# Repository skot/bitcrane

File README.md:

Bitcrane can fully control a Bitmain Antminer over a single USB connection.

- CERN Open Hardware License (OHL) v2
- [KiCad](https://kicad.org) design files
- Based on the Raspberry Pi RP2040
- Support for 3 Antminer hashboards
- Support for 4 fans with your choice of 1x4 or 2x2 connectors
- Controls Antminer S19/S21 style PSUs
- Bitcrane is powered by 5V from the USB-C connector
	- Attached fans are powered by standard Antminer 2x3 12V controlboard power

## TODO
- RP2040 firmware, based on [emberone-usbserial-fw](https://github.com/256foundation/emberone-usbserial-fw/tree/bitcrane-v3) bitcrane-v3 branch WIP
- [Mujina](https://mujina.org) mining firmware support.
- Custom Antminer faceplate.
- [Dismantle the proprietary Bitcoin mining empire](https://256foundation.org)

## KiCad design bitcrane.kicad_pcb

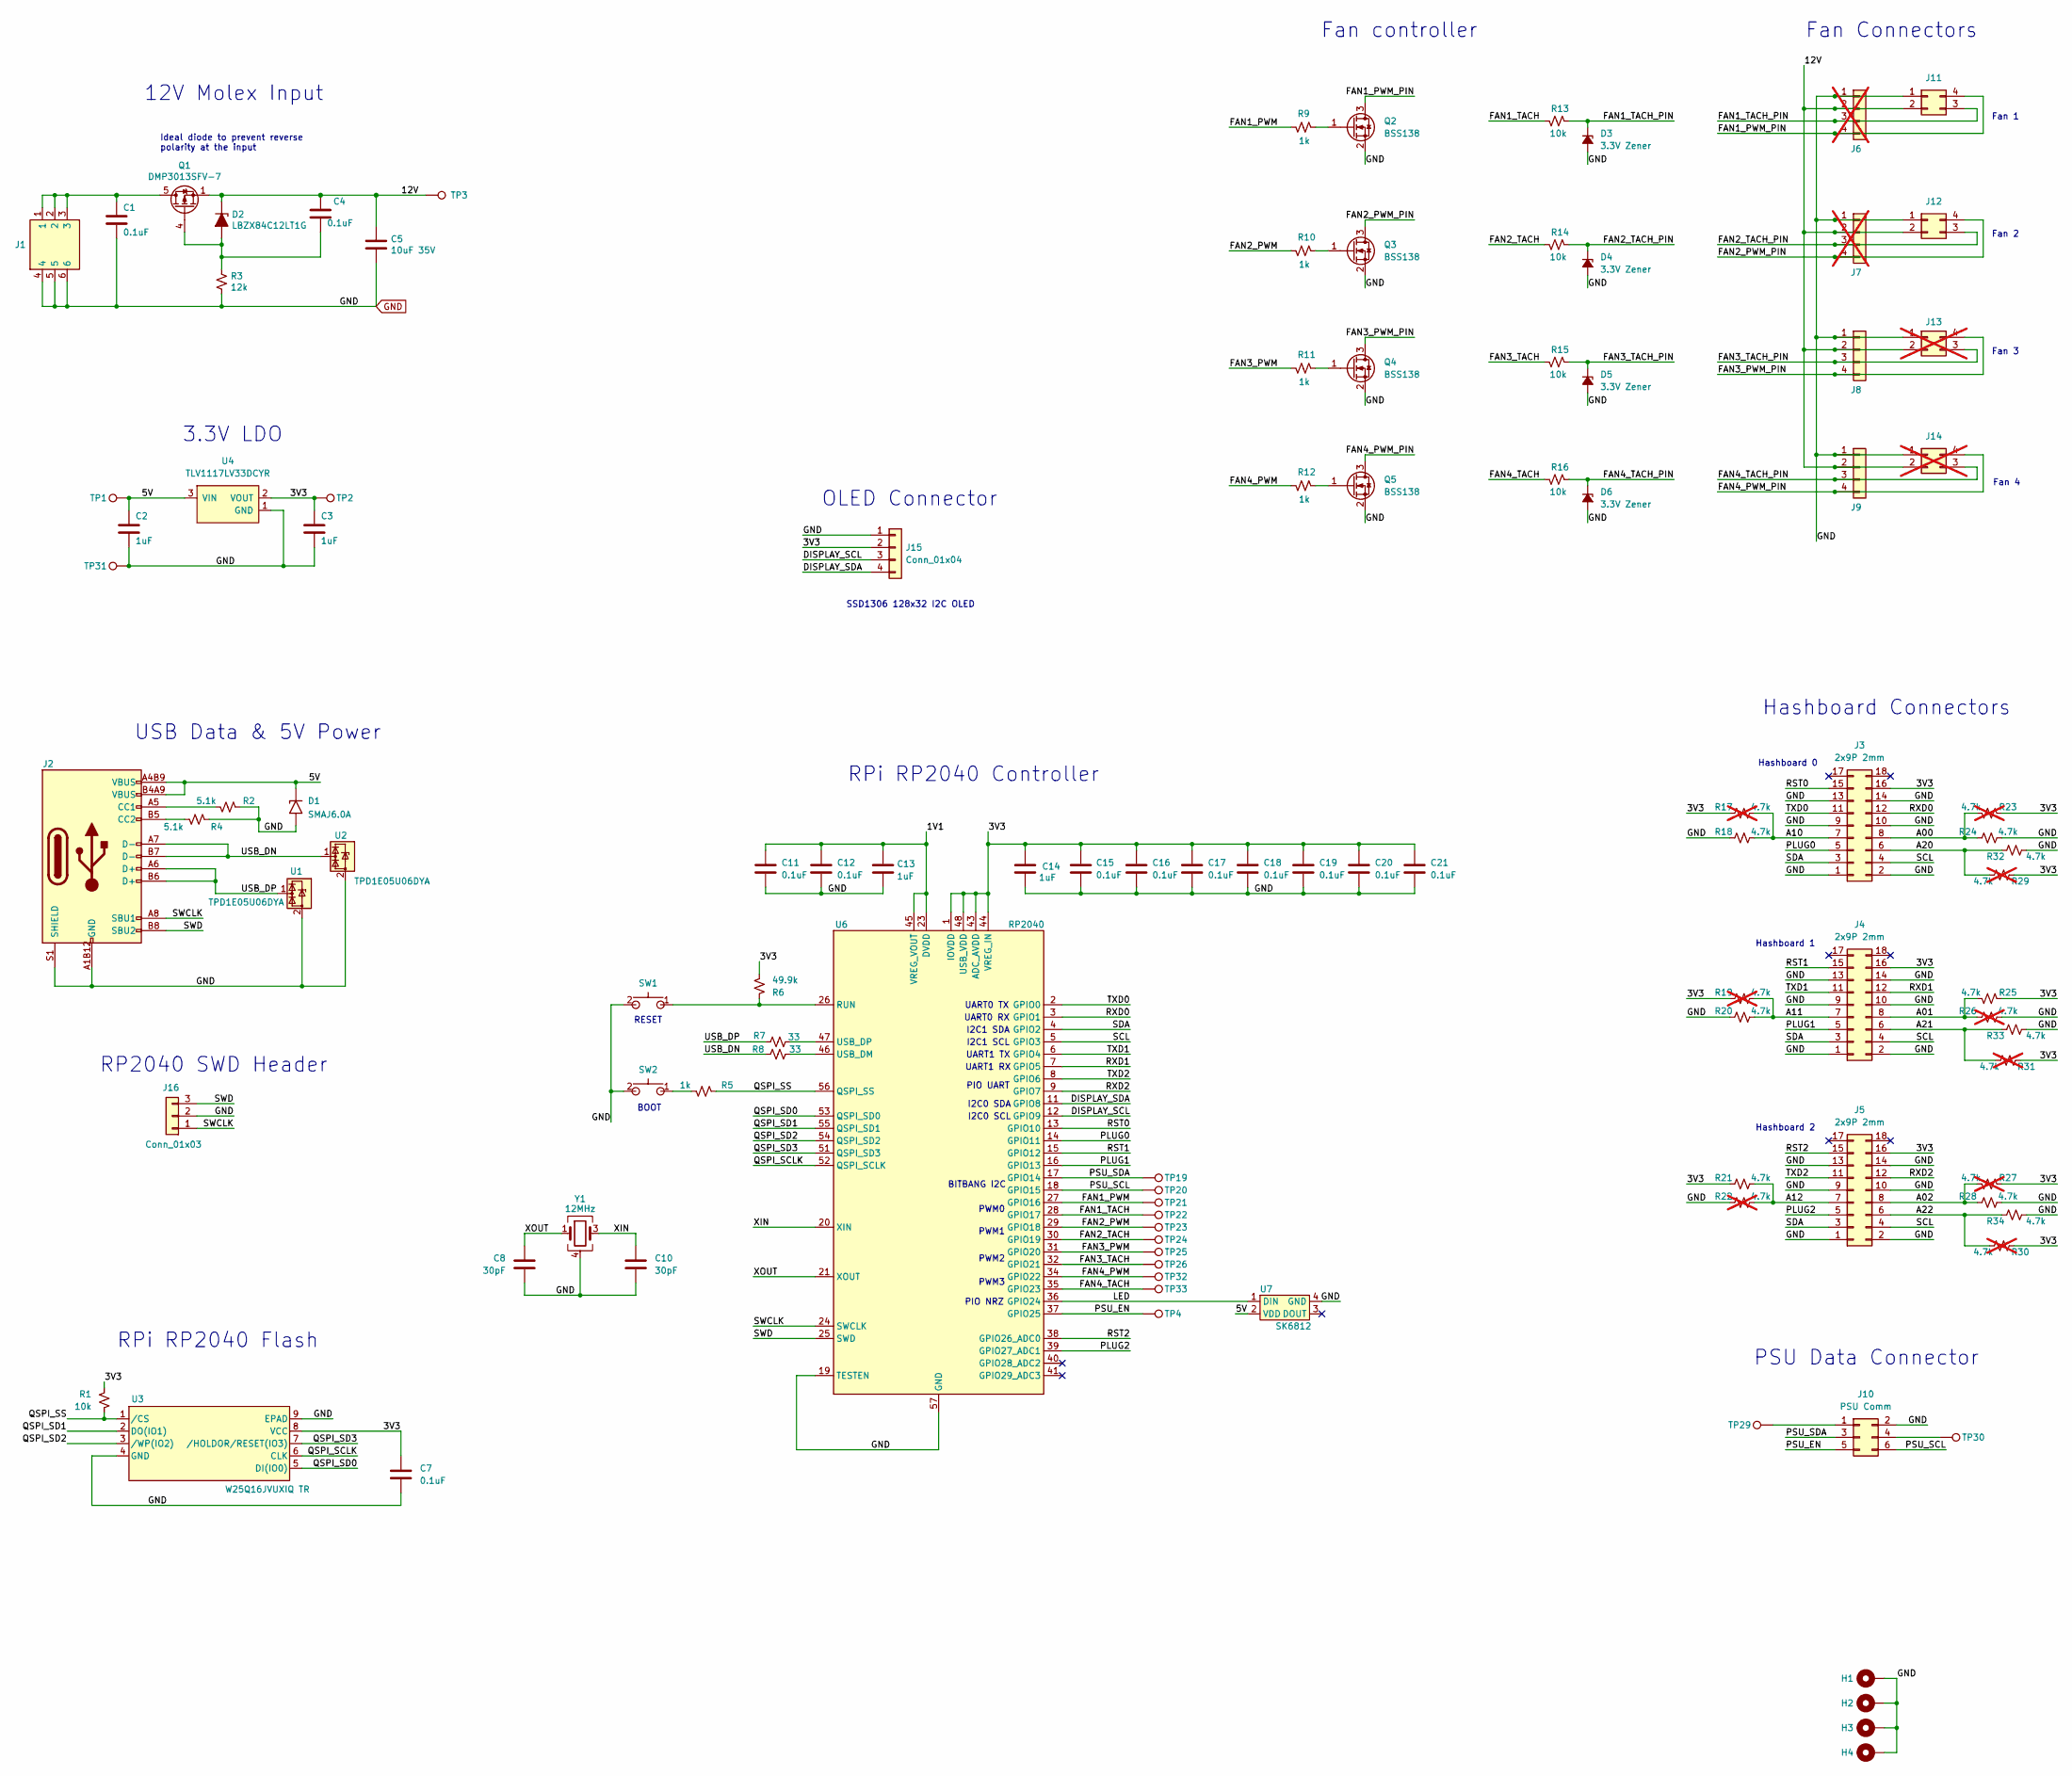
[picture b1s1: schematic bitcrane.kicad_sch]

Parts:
C1, C4, C7, C11, C12, C15, C16, C17, C18, C19, C20, C21: 0.1uF; C_0402_1005Metric; LCSC C307331
C2, C3, C13, C14: 1uF; C_0402_1005Metric; LCSC C52923
C5: 10uF 35V; C_0805_2012Metric; LCSC C440198
C8, C10: 30pF; C_0402_1005Metric; LCSC C1570
D1: SMAJ6.0A; D_SMB; LCSC C364284
D2: LBZX84C12LT1G; SOT-23-3_L2.9-W1.6-P1.90-LS2.8-BR; LCSC C12773
D3, D4, D5, D6: 3.3V Zener; D_SOD-123; LCSC C2112
H1, H2, H3, H4: MountingHole_Pad; MountingHole_3mm_Pad
J1: 0455580003; CONN-TH_50362462; LCSC C492365
J2: USB_C_Receptacle_USB2.0; USB_C_Receptacle_GCT_USB4105-xx-A_16P_TopMnt_Horizontal; LCSC C2988369
J3, J4, J5: 2x9P 2mm; CONN-TH_X2026WV-2-09D-46SN; LCSC C437089
J6, J7: 61900411021; CONN-TH_4P-P2.54_HCTL_HC-2510-4AW; PARTNO 61900411021; LCSC C2982043; not fitted
J8, J9: 61900411021; CONN-TH_4P-P2.54_HCTL_HC-2510-4AW; LCSC C2982043
J10: PSU Comm; CONN-TH_6P-P2.00_PHD-2X3A; LCSC C2845614
J11, J12: 0353180420; CONN-TH_4P-P4.20_5557-2X2AW; LCSC C54909
J13, J14: 0353180420; CONN-TH_4P-P4.20_5557-2X2AW; PARTNO 0353180420; LCSC C54909; not fitted
J15: Conn_01x04; PinHeader_1x04_P2.54mm_Vertical_shifted
J16: Conn_01x03; PinHeader_1x03_P2.54mm_Vertical
Q1: DMP3013SFV-7; POWERPAK-1212-8_L3.1-W3.1-P0.65-LS3.3-BL; LCSC C264098
Q2, Q3, Q4, Q5: BSS138; SOT-23; LCSC C5248642
R1, R13, R14, R15, R16: 10k; R_0402_1005Metric; LCSC C25744
R2, R4: 5.1k; R_0402_1005Metric; LCSC C25905
R3: 12k; R_0402_1005Metric; LCSC C25752
R5, R9, R10, R11, R12: 1k; R_0402_1005Metric; LCSC C106235
R6: 49.9k; R_0402_1005Metric; LCSC C25897
R7, R8: 33; R_0402_1005Metric; LCSC C25105
R17, R19, R22, R23, R26, R27, R29, R30, R31: 4.7k; R_0402_1005Metric; LCSC C25900; not fitted
R18, R20, R21, R24, R25, R28, R32, R33, R34: 4.7k; R_0402_1005Metric; LCSC C25900
SW1, SW2: TS-1088-AR02016; SW-SMD_L3.9-W3.0-P4.45; LCSC C720477
TP1: 5V; TestPoint_Pad_D1.0mm
TP2: 3V3; TestPoint_Pad_D1.0mm
TP3: 12V; TestPoint_Pad_D1.0mm
TP4: PSU_EN; TestPoint_Pad_D1.0mm
TP19: SDA; TestPoint_Pad_D1.0mm
TP20: SCL; TestPoint_Pad_D1.0mm
TP21, TP23, TP25, TP32: PWM; TestPoint_Pad_D1.0mm
TP22, TP24, TP26, TP33: TACH; TestPoint_Pad_D1.0mm
TP29, TP30: TestPoint; TestPoint_Pad_D1.0mm
TP31: GND; TestPoint_Pad_D1.0mm
U1, U2: TPD1E05U06DYA; D_SOD-523; LCSC C3702980
U3: W25Q16JVUXIQ TR; USON-8_UX_2x3x0p6_WIN; LCSC C2843335
U4: TLV1117LV33DCYR; VREG_TLV1117LV33DCYR; LCSC C15578
U6: RP2040; QFN-56-1EP_7x7mm_P0.4mm_EP3.2x3.2mm; LCSC C2040
U7: SK6812; LED-SMD_4P-L4.0-W1.6-L; LCSC C5378737
Y1: 12MHz; XTAL_ECS-120-20-33-CKM-TR3; LCSC C9002

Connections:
/1V1: C11.2, C12.2, C13.2, U6.23 (DVDD), U6.45 (VREG_VOUT), U6.50 (DVDD)
/3V3: C3.1, C7.2, C14.2, C15.2, C16.2, C17.2, C18.2, C19.2, C20.2, C21.2, J3.16, J4.16, J5.16, J15.2, R1.1, R6.2, R17.1, R19.1, R21.1, R23.1, R25.1, R27.1, R29.1, R30.1, R31.1, TP2.1, U3.8 (VCC), U4.2 (VOUT), U4.4 (VOUT), U6.1 (IOVDD), U6.10 (IOVDD), U6.22 (IOVDD), U6.33 (IOVDD), U6.42 (IOVDD), U6.43 (ADC_AVDD), U6.44 (VREG_IN), U6.48 (USB_VDD), U6.49 (IOVDD)
/5V: C2.1, D1.1 (A1), J2.A4B9 (VBUS), J2.B4A9 (VBUS), TP1.1, U4.3 (VIN), U7.2 (VDD)
/12V: C4.1, C5.1, D2.3 (K), J6.2, J7.2, J8.2, J9.2, J11.2, J12.2, J13.2, J14.2, Q1.1 (S), Q1.2 (S), Q1.3 (S), TP3.1
/A00: J3.8, R23.2, R24.1
/A01: J4.8, R25.2, R26.1
/A02: J5.8, R27.2, R28.1
/A10: J3.7, R17.2, R18.2
/A11: J4.7, R19.2, R20.2
/A12: J5.7, R21.2, R22.2
/A20: J3.6, R29.2, R32.1
/A21: J4.6, R31.2, R33.1
/A22: J5.6, R30.2, R34.1
/DISPLAY_SCL: J15.3, U6.12 (GPIO9)
/DISPLAY_SDA: J15.4, U6.11 (GPIO8)
/FAN1_PWM: R9.2, TP21.1, U6.27 (GPIO16)
/FAN1_PWM_PIN: J6.4, J11.4, Q2.3 (D)
/FAN1_TACH: R13.2, TP22.1, U6.28 (GPIO17)
/FAN1_TACH_PIN: D3.1 (K), J6.3, J11.3, R13.1
/FAN2_PWM: R10.2, TP23.1, U6.29 (GPIO18)
/FAN2_PWM_PIN: J7.4, J12.4, Q3.3 (D)
/FAN2_TACH: R14.2, TP24.1, U6.30 (GPIO19)
/FAN2_TACH_PIN: D4.1 (K), J7.3, J12.3, R14.1
/FAN3_PWM: R11.2, TP25.1, U6.31 (GPIO20)
/FAN3_PWM_PIN: J8.4, J13.4, Q4.3 (D)
/FAN3_TACH: R15.2, TP26.1, U6.32 (GPIO21)
/FAN3_TACH_PIN: D5.1 (K), J8.3, J13.3, R15.1
/FAN4_PWM: R12.2, TP32.1, U6.34 (GPIO22)
/FAN4_PWM_PIN: J9.4, J14.4, Q5.3 (D)
/FAN4_TACH: R16.2, TP33.1, U6.35 (GPIO23)
/FAN4_TACH_PIN: D6.1 (K), J9.3, J14.3, R16.1
/LED: U6.36 (GPIO24), U7.1 (DIN)
/PLUG0: J3.5, U6.14 (GPIO11)
/PLUG1: J4.5, U6.16 (GPIO13)
/PLUG2: J5.5, U6.39 (GPIO27_ADC1)
/PSU_EN: J10.5, TP4.1, U6.37 (GPIO25)
/PSU_SCL: J10.6, TP20.1, U6.18 (GPIO15)
/PSU_SDA: J10.3, TP19.1, U6.17 (GPIO14)
/QSPI_SCLK: U3.6 (CLK), U6.52 (QSPI_SCLK)
/QSPI_SD0: U3.5 (DI(IO0)), U6.53 (QSPI_SD0)
/QSPI_SD1: U3.2 (DO(IO1)), U6.55 (QSPI_SD1)
/QSPI_SD2: U3.3 (/WP(IO2)), U6.54 (QSPI_SD2)
/QSPI_SD3: U3.7 (/HOLDOR/RESET(IO3)), U6.51 (QSPI_SD3)
/QSPI_SS: R1.2, R5.1, U3.1 (/CS), U6.56 (QSPI_SS)
/RST0: J3.15, U6.13 (GPIO10)
/RST1: J4.15, U6.15 (GPIO12)
/RST2: J5.15, U6.38 (GPIO26_ADC0)
/RXD0: J3.12, U6.3 (GPIO1)
/RXD1: J4.12, U6.7 (GPIO5)
/RXD2: J5.12, U6.9 (GPIO7)
/SCL: J3.4, J4.4, J5.4, U6.5 (GPIO3)
/SDA: J3.3, J4.3, J5.3, U6.4 (GPIO2)
/SWCLK: J2.A8 (SBU1), J16.1, U6.24 (SWCLK)
/SWD: J2.B8 (SBU2), J16.3, U6.25 (SWD)
/TXD0: J3.11, U6.2 (GPIO0)
/TXD1: J4.11, U6.6 (GPIO4)
/TXD2: J5.11, U6.8 (GPIO6)
/USB_DN: J2.A7 (D-), J2.B7 (D-), R8.1, U2.1 (I/O)
/USB_DP: J2.A6 (D+), J2.B6 (D+), R7.1, U1.1 (I/O)
/XIN: C10.2, U6.20 (XIN), Y1.3
/XOUT: C8.2, U6.21 (XOUT), Y1.1
GND: C1.2, C2.2, C3.2, C5.2, C7.1, C8.1, C10.1, C11.1, C12.1, C13.1, C14.1, C15.1, C16.1, C17.1, C18.1, C19.1, C20.1, C21.1, D1.2 (A2), D3.2 (A), D4.2 (A), D5.2 (A), D6.2 (A), H1.1, H2.1, H3.1, H4.1, J1.4, J1.5, J1.6, J2.A1B12 (GND), J2.B1A12 (GND), J2.S1 (SHIELD), J3.1, J3.2, J3.9, J3.10, J3.13, J3.14, J4.1, J4.2, J4.9, J4.10, J4.13, J4.14, J5.1, J5.2, J5.9, J5.10, J5.13, J5.14, J6.1, J7.1, J8.1, J9.1, J10.2, J11.1, J12.1, J13.1, J14.1, J15.1, J16.2, Q2.2 (S), Q3.2 (S), Q4.2 (S), Q5.2 (S), R2.1, R3.2, R4.1, R18.1, R20.1, R22.1, R24.2, R26.2, R28.2, R32.2, R33.2, R34.2, SW1.2, SW2.2, TP31.1, U1.2 (GND), U2.2 (GND), U3.4 (GND), U3.9 (EPAD), U4.1 (GND), U6.19 (TESTEN), U6.57 (GND), U7.4 (GND), Y1.2, Y1.4
unnamed: C1.1, J1.1, J1.2, J1.3, Q1.5 (D), Q1.6 (D), Q1.7 (D), Q1.8 (D)
unnamed: C4.2, D2.1 (A), Q1.4 (G), R3.1
unnamed: J2.A5 (CC1), R2.2
unnamed: J2.B5 (CC2), R4.2
unnamed: J10.1, TP29.1
unnamed: J10.4, TP30.1
unnamed: Q2.1 (G), R9.1
unnamed: Q3.1 (G), R10.1
unnamed: Q4.1 (G), R11.1
unnamed: Q5.1 (G), R12.1
unnamed: R5.2, SW2.1
unnamed: R6.1, SW1.1, U6.26 (RUN)
unnamed: R8.2, U6.46 (USB_DM)
unnamed: R7.2, U6.47 (USB_DP)

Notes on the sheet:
OLED Connector
Fan 2
PWM1
PSU Data Connector
PIO NRZ
Fan 3
PIO UART
Fan controller
I2C0 SDA
PWM0
RP2040 SWD Header
Hashboard 1
I2C0 SCL
I2C1 SDA
Hashboard Connectors
USB Data & 5V Power
PWM3
Fan 4
BOOT
Fan Connectors
Ideal diode to prevent reverse polarity at the input
Hashboard 2
Fan 1
RPi RP2040 Flash
UART0 TX
RPi RP2040 Controller
UART1 RX
UART1 TX
Hashboard 0
3.3V LDO
I2C1 SCL
PWM2
12V Molex Input
RESET
SSD1306 128x32 I2C OLED
BITBANG I2C
UART0 RX

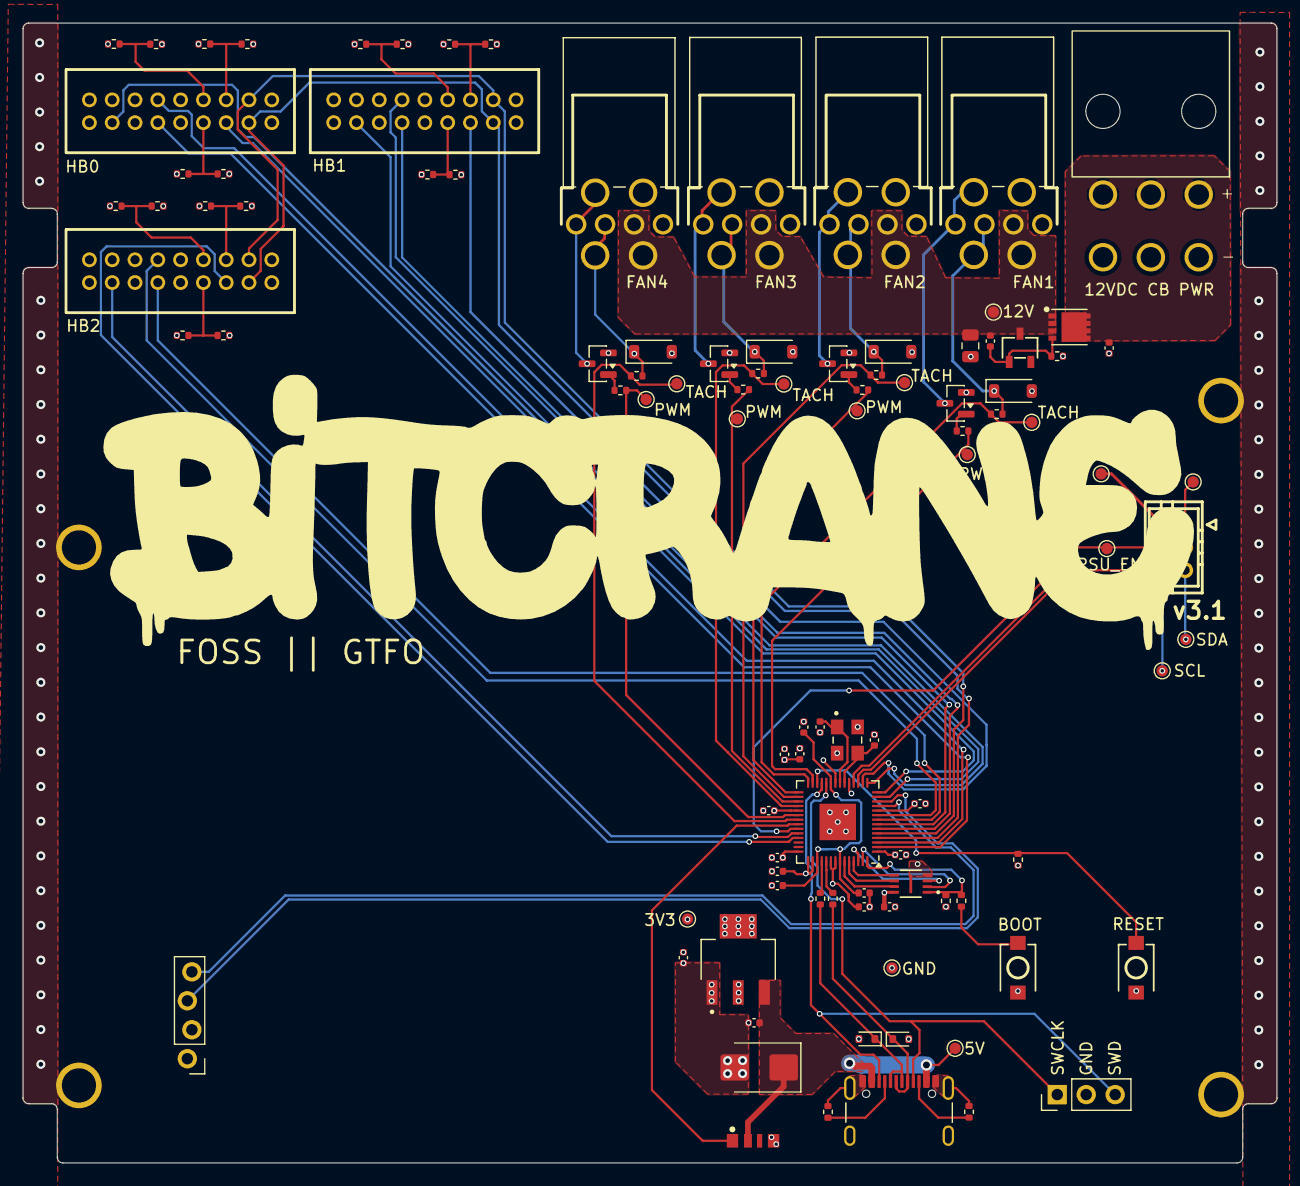
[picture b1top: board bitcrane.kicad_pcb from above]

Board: 4 copper layers, 110.0 x 100.0 mm, 110 parts (0 on the bottom side), 76 nets.

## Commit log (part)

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2023-10-23 initial import
2023-10-24 added most of the schematic
2023-10-24 routed
2023-10-24 added the fan controller IC. silkscreen cleanup
2023-10-24 cleanup. updated render
2023-11-06 added test points, filled out BOM, ran DRC
2023-11-06 couple small gerber fixes. updated render
2023-11-06 cleanup
2023-11-10 fixed 12V label position ;P
2023-12-07 added fixes for #2 #3 #4 to schematic. still needs to be adjusted in layout
2023-12-07 added fix for #5 to schematic. still needs PCB work
2023-12-08 routed v2 changes
2023-12-09 switched to 3 HB connectors. added I2C hub. routed
2023-12-09 ran DRC, fixed errors, generated gerbers, generated BOM
2023-12-10 removed paste from THT parts :P
2023-12-10 last minute fix for #1
2024-01-11 fix for #8. regenerated gerbers. bump version to 2.1
2024-03-20 fix for #9. regenerated gerbers. bumped version to 2.2
2024-04-08 adding iBOM for assembly
2024-05-03 fix for #10 small DRC fixes. updated to v2.3
2024-05-06 added PCB labels for Fans and Hashboards. Starting to add LCSC part numbers
2024-05-06 added almost all LCSC part numbers
2024-05-06 added gerbers and BOM
2024-05-06 Updated all footprints for JLCPCB parts. Added JLCPCB BOM and CPL
2024-05-06 readme update
2024-05-07 actually add manufacturing files this time..
2024-05-08 digikey parts BOM
2024-05-08 digikey part numbers, changed value c18/c21 from 47uF to 4.7uF
2024-05-08 add GPL LICENSE
2024-05-08 digikey BOM
2024-05-09 c18 c21 value from 47uF to 4.7uF on cchematic
2024-05-14 Crane Art
2024-05-23 changed Y1 LCSC partnumber for #12 Changed C18/C21 value in schematic (thanks @BeeEvolved)
2024-05-23 update render
2025-11-17 drc updates
2025-11-17 switch schematic to RP2350. PCB not updated yet
2025-11-17 removed FTDI and EMC2305 from schematic and PCB
2025-11-17 switched to discrete fan control. wired up RP2040 added worksheet logo
2025-11-17 remove old gerbers
2025-11-17 switch license to OHL v2
2025-11-18 rough PCB routing done
2025-11-18 Revise README with project details and TODOs
    Updated README to enhance project description and features.
2025-11-18 switch to bigger 3.3V LDO. add 3D parts
2025-11-18 drc check. copy over missing footprints to bitcrane library
2025-11-18 add more 3D files. rotate display 180
2025-11-18 change buttons to LCSC versions. add preliminary LCSC part numbers for everything
2025-11-18 removed old libraries
2025-11-19 update test points and cleanup silkscreen. add render to readme.
2025-12-18 Add link to RP2040 bitcrane v3 firmware
2026-01-14 add SWD header for #14
2026-03-09 Update TODO with new firmware reference

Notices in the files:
bitcrane.kicad_sch:
CERN OHL v2
